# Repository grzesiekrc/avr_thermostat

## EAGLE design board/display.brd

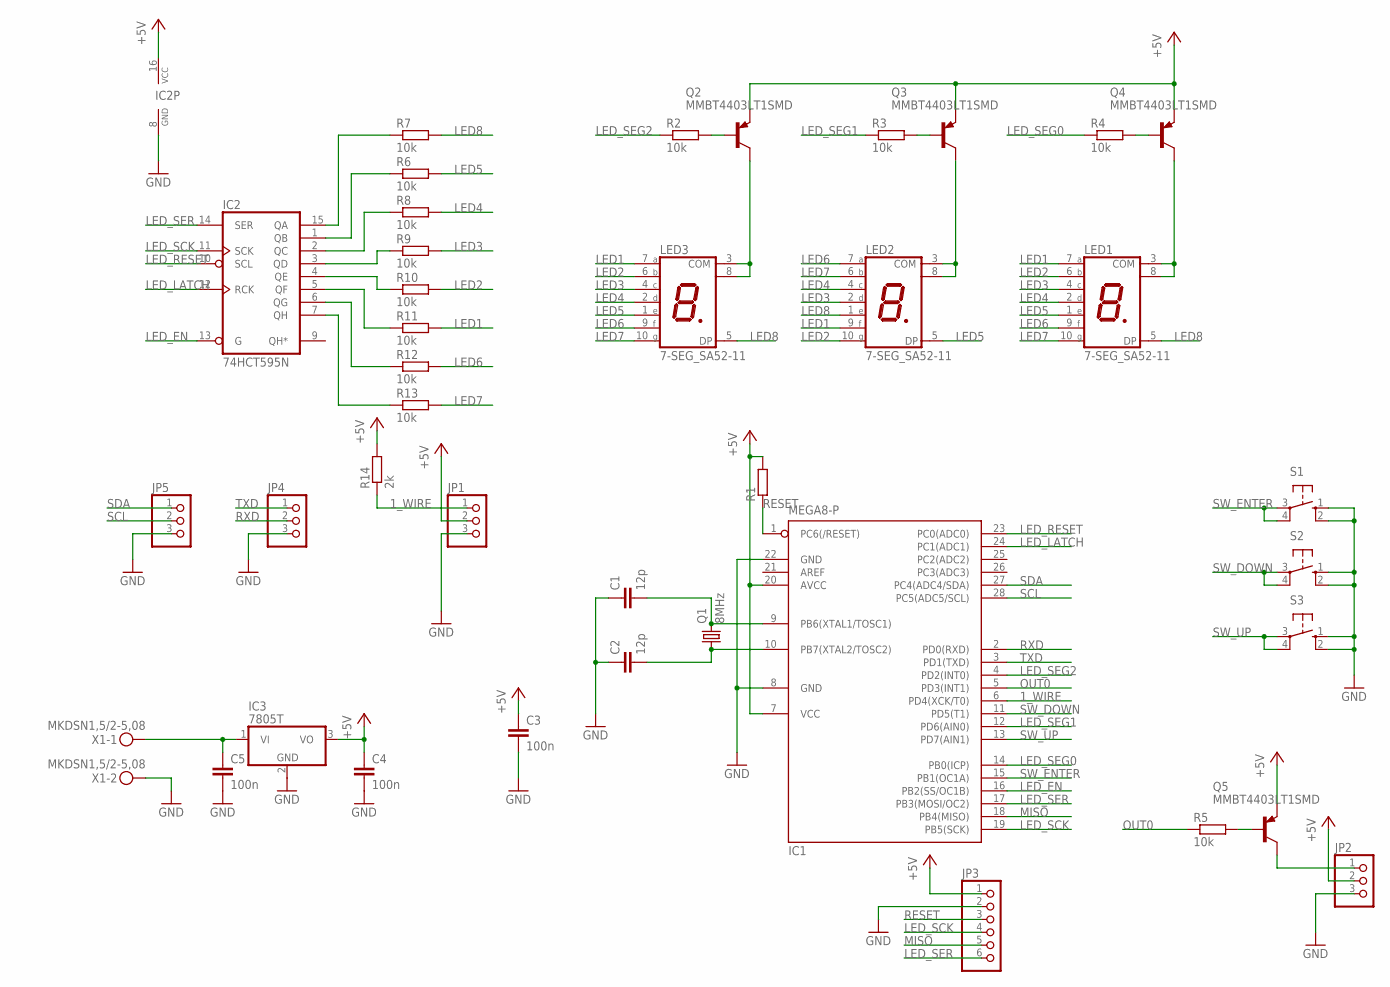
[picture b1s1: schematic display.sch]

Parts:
C1, C2: 12p; C050-035X075
C3, C4, C5: 100n; C050-030X075
IC1: MEGA8-P; DIL28-3
IC2: 74HCT595N; DIL16
IC3: 7805T; TO220H
JP1, JP2, JP4, JP5: PINHD-1X3; 1X03
JP3: PINHD-1X6; 1X06
LED1, LED2, LED3: 7-SEG_SA52-11; SA52-11
Q1: 8MHz; HC49U70
Q2, Q3, Q4, Q5: MMBT4403LT1SMD; SOT23-BEC
R1: R-EU_R1206; R1206
R2, R3, R4, R5, R6, R7, R8, R9, R10, R11, R12, R13: 10k; M1206
R14: 2k; M1206
S1, S2, S3: 10-XX; B3F-10XX
X1: MKDSN1,5/2-5,08

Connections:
1_WIRE: IC1.6 (PD4(XCK/T0)), JP1.1, R14.1
+5V: C3.1, C4.1, IC1.7 (VCC), IC1.20 (AVCC), IC2.16 (VCC), IC3.3 (VO), JP1.2, JP2.2, JP3.1, Q2.E, Q3.E, Q4.E, Q5.E, R1.2, R14.2
GND: C1.1, C2.1, C3.2, C4.2, C5.2, IC1.8 (GND), IC1.22 (GND), IC2.8 (GND), IC3.2 (GND), JP1.3, JP2.3, JP3.2, JP4.3, JP5.3, S1.1 (S), S1.2 (S1), S2.1 (S), S2.2 (S1), S3.1 (S), S3.2 (S1), X1.2
LED1: LED1.7 (A), LED2.9 (F), LED3.7 (A), R11.2
LED2: LED1.6 (B), LED2.10 (G), LED3.6 (B), R10.2
LED3: LED1.4 (C), LED2.2 (D), LED3.4 (C), R9.2
LED4: LED1.2 (D), LED2.4 (C), LED3.2 (D), R8.2
LED5: LED1.1 (E), LED2.5 (DP), LED3.1 (E), R6.2
LED6: LED1.9 (F), LED2.7 (A), LED3.9 (F), R12.2
LED7: LED1.10 (G), LED2.6 (B), LED3.10 (G), R13.2
LED8: LED1.5 (DP), LED2.1 (E), LED3.5 (DP), R7.2
LED_EN: IC1.16 (PB2(SS/OC1B)), IC2.13 (G)
LED_LATCH: IC1.24 (PC1(ADC1)), IC2.12 (RCK)
LED_RESET: IC1.23 (PC0(ADC0)), IC2.10 (SCL)
LED_SCK: IC1.19 (PB5(SCK)), IC2.11 (SCK), JP3.4
LED_SEG0: IC1.14 (PB0(ICP)), R4.1
LED_SEG1: IC1.12 (PD6(AIN0)), R3.1
LED_SEG2: IC1.4 (PD2(INT0)), R2.1
LED_SER: IC1.17 (PB3(MOSI/OC2)), IC2.14 (SER), JP3.6
MISO: IC1.18 (PB4(MISO)), JP3.5
unnamed: C1.2, IC1.9 (PB6(XTAL1/TOSC1)), Q1.2
unnamed: C2.2, IC1.10 (PB7(XTAL2/TOSC2)), Q1.1
unnamed: LED3.3 (COM), LED3.8 (COM), Q2.C
unnamed: IC2.15 (QA), R7.1
unnamed: LED1.3 (COM), LED1.8 (COM), Q4.C
unnamed: LED2.3 (COM), LED2.8 (COM), Q3.C
unnamed: Q2.B, R2.2
unnamed: Q3.B, R3.2
unnamed: Q4.B, R4.2
unnamed: Q5.B, R5.2
unnamed: JP2.1, Q5.C
unnamed: IC2.1 (QB), R6.1
unnamed: IC2.2 (QC), R8.1
unnamed: IC2.3 (QD), R9.1
unnamed: IC2.4 (QE), R10.1
unnamed: IC2.5 (QF), R11.1
unnamed: IC2.6 (QG), R12.1
unnamed: IC2.7 (QH), R13.1
unnamed: C5.1, IC3.1 (VI), X1.1
OUT0: IC1.5 (PD3(INT1)), R5.1
RESET: IC1.1 (PC6(/RESET)), JP3.3, R1.1
RXD: IC1.2 (PD0(RXD)), JP4.2
SCL: IC1.28 (PC5(ADC5/SCL)), JP5.2
SDA: IC1.27 (PC4(ADC4/SDA)), JP5.1
SW_DOWN: IC1.11 (PD5(T1)), S2.3, S2.4 (P1)
SW_ENTER: IC1.15 (PB1(OC1A)), S1.3, S1.4 (P1)
SW_UP: IC1.13 (PD7(AIN1)), S3.3, S3.4 (P1)
TXD: IC1.3 (PD1(TXD)), JP4.1

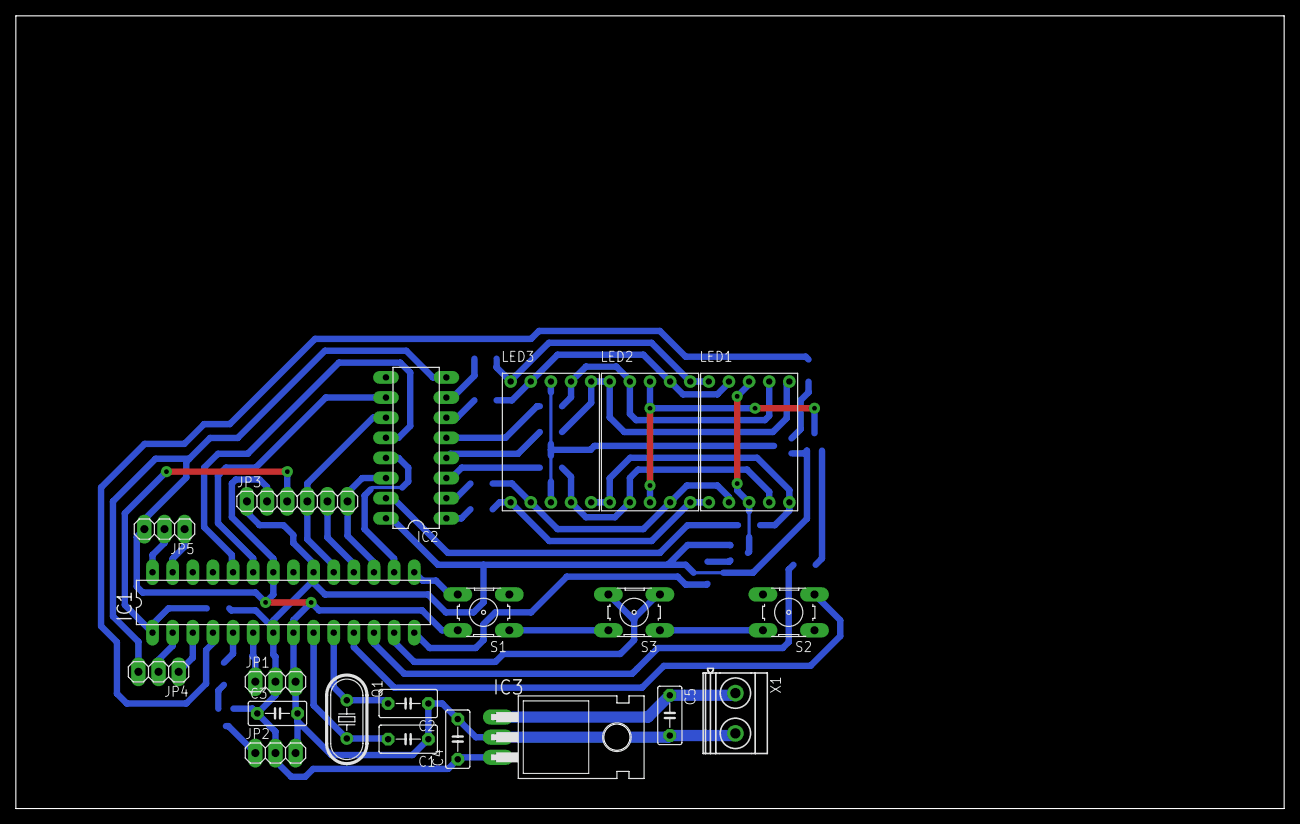
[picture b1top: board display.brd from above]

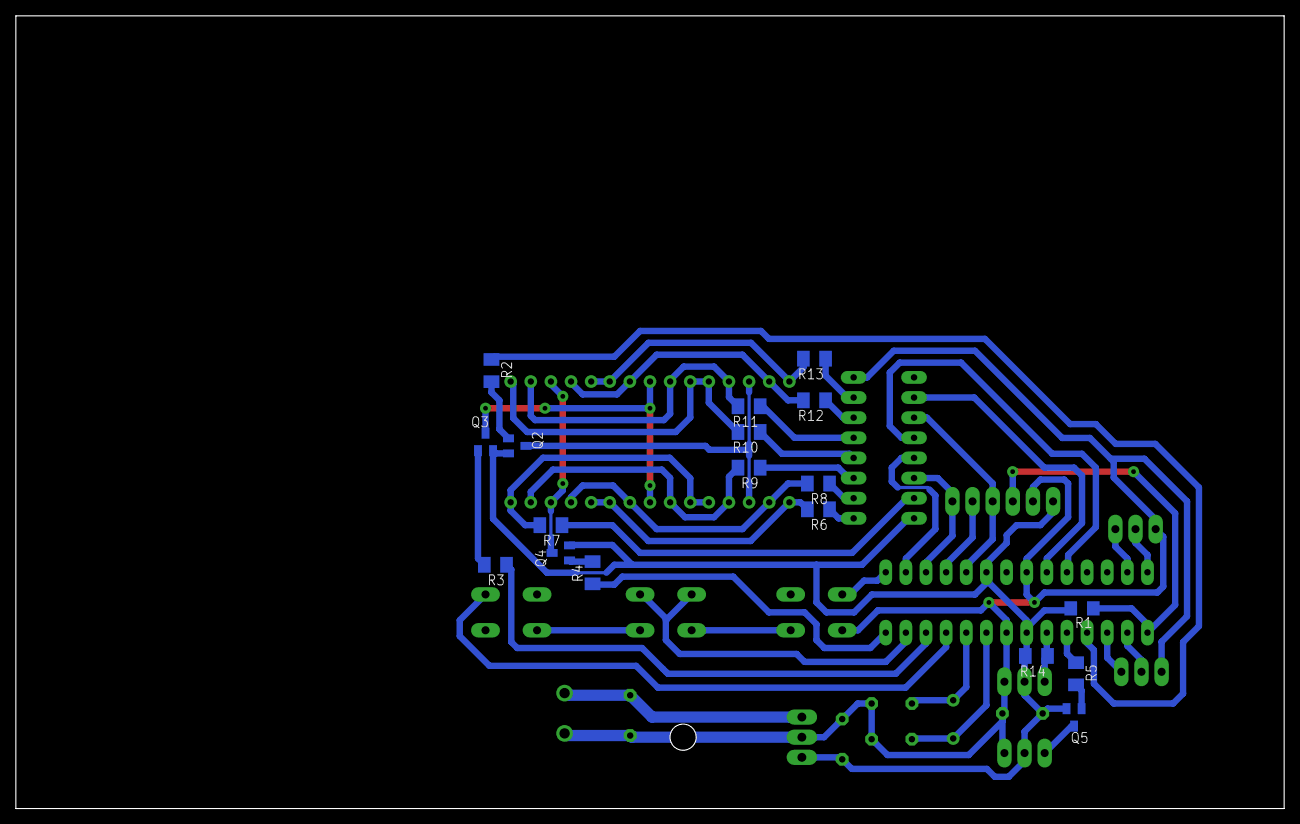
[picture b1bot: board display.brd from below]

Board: 2 copper layers, 160.0 x 100.0 mm, 39 parts (18 on the bottom side), 48 nets.

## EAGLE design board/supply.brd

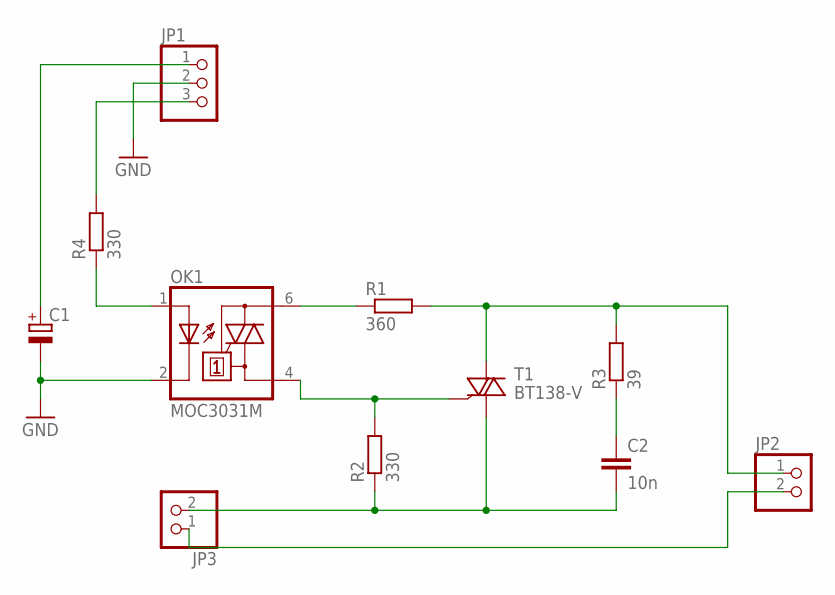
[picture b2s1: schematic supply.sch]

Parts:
C1: CPOL-EUE5-10.5; E5-10,5
C2: 10n; C102-064X133
JP1: PINHD-1X3; 1X03
JP2, JP3: PINHD-1X2; 1X02
OK1: MOC3031M; DIL06
R1: 360; 0207/10
R2, R4: 330; 0207/10
R3: 39; 0207/10
T1: BT138-V; TO220BV

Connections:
GND: C1.-, JP1.2, OK1.2 (C)
unnamed: OK1.1 (A), R4.1
unnamed: OK1.6 (A2), R1.1
unnamed: JP2.1, R1.2, R3.2, T1.T2 (A2)
unnamed: OK1.4 (A1), R2.2, T1.G
unnamed: C2.2, JP3.2, R2.1, T1.T1 (A1)
unnamed: C2.1, R3.1
unnamed: JP1.3, R4.2
unnamed: C1.+, JP1.1
unnamed: JP2.2, JP3.1

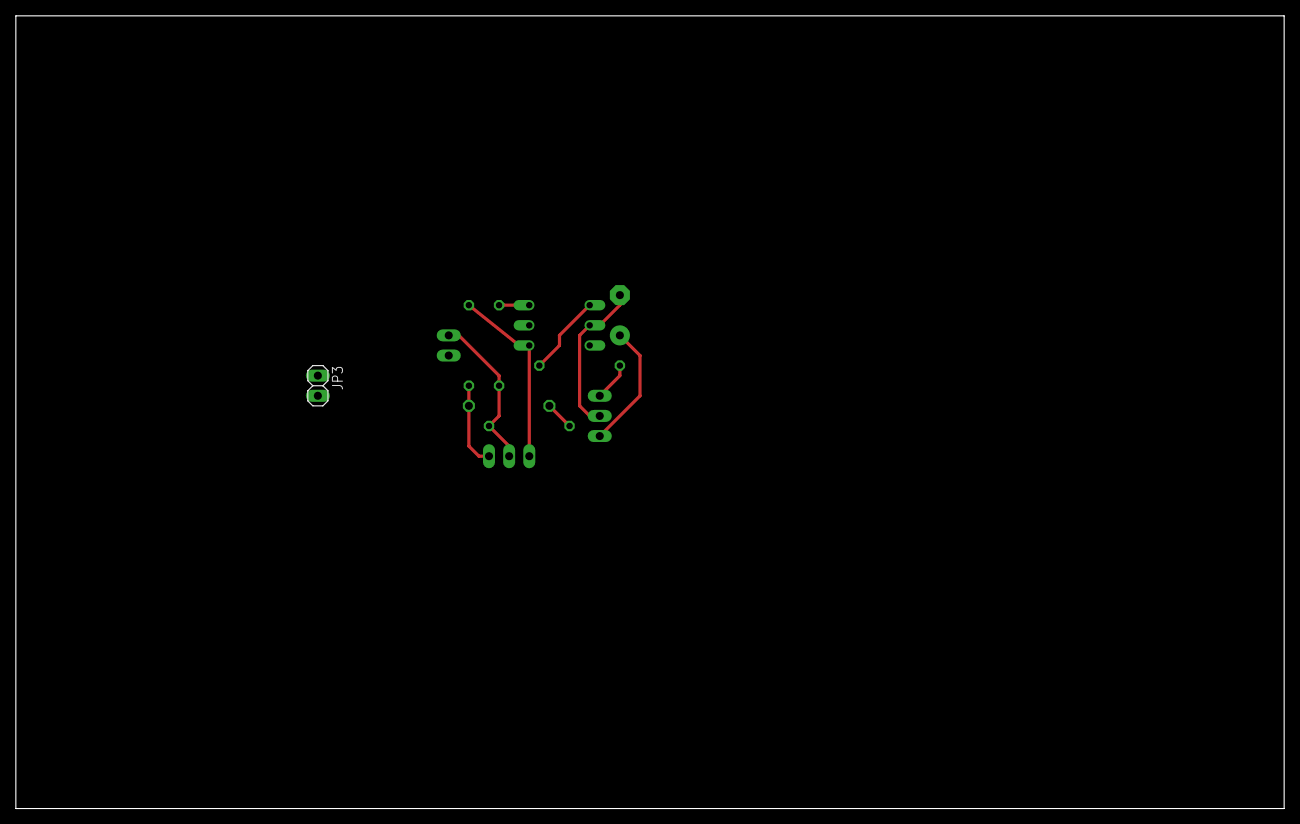
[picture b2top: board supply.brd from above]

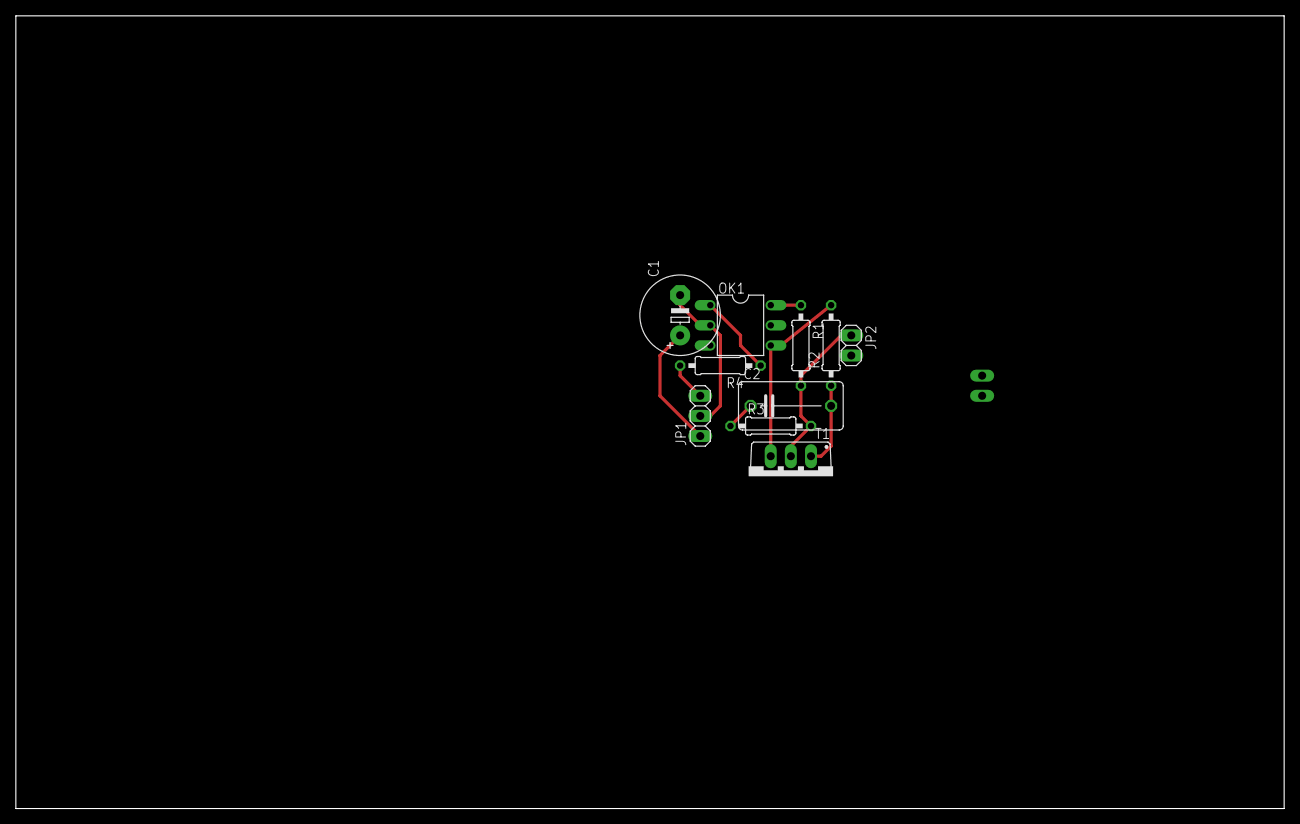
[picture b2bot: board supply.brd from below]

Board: 2 copper layers, 160.0 x 100.0 mm, 11 parts (10 on the bottom side), 10 nets.

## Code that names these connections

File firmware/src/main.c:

/*
 * main.c
 *
 *  Created on: 14 wrz 2023
 *      Author: grzesiek
 */

#include <avr/io.h>
#include <avr/interrupt.h>

#include "1wire.h"
#include "display.h"
#include "output_control.h"
#include "buttons.h"
#include "utils.h"
int16_t temperature = 0;

volatile uint8_t timCounter;
volatile uint8_t seconds = 0;

ISR(TIMER0_OVF_vect)
{
	if(++timCounter > TIM_SECOND_COUNTER_MAX)
	{
		seconds++;
		timCounter = 0;
	}
}

void sendByte(uint8_t byte)
{
	while (!(UCSRA & (1<<UDRE)));
	UDR = byte;
}

void printTemperature(int16_t value)
{
	if (value < 0)
	{
		sendByte('-');
		value *= -1;
	}

	uint8_t digits[10];
	int8_t i = 0;

	while (value > 0)
	{
		digits[i++] = (value % 10) + '0';
		value /= 10;
	}

	i--;

	while (i > 0)
	{
		sendByte(digits[i--]);
	}
	sendByte('.');
	sendByte(digits[0]);
	sendByte('*');//Celsius degree sign
	sendByte('C');
}

void processTimer(void)
{
	static uint16_t prevSeconds;
	if(prevSeconds != seconds)
	{
		displaySecondElapsed();
		prevSeconds = seconds;
		sendByte('\r');
		printTemperature(temperature);
		sendByte(' ');
		sendByte(' ');
		sendByte(' ');
	}
}

int main(void)
{
	DDRB = (1<<PB0) | (1<<PB2) | (1<<PB3) | (1<<PB5);
	DDRC = (1<<PC0) | (1<<PC1);
	DDRD = (1<<PD1) | (1<<PD2) | (1<<PD3) | (1<<PD6);
	PORTD = (1<<PD5) | (1<<PD7);

	PORTB = (1<<PB1);

	UBRRH = 0;
	UBRRL = (unsigned char)51;

	//UCSRB = (1<<TXEN) | (1<<RXEN) | (1<<TXCIE) | (1<<RXCIE) | (1<<UCSZ2);
	UCSRB = (1<<TXEN) | (1<<RXEN) | (1<<RXCIE);
	UCSRC = (1<<URSEL) | (1<<UCSZ1) | (1<<UCSZ0);

	TCCR0 = (1<<CS02) | (1<<CS00);

	TCCR1A = (1<<WGM10) | (1<<COM1B1) | (1<<COM1B0);
	TCCR1B = (1<<WGM12) | (1<<CS11) | (1<<CS10);

	TIMSK = (1<<TOIE0);

	SPCR = (1<<SPIE) | (1<<SPE) | (1<<MSTR) | (1<<SPR1) | (1<<SPR0);

	BRIGHTNESS(255);

	OUTPUT_OFF();

	sei();

	displayInit();

	while(1)
	{
		temperature = readTemperature();
		temperatureNotification(temperature);
		processButtons();
		processTimer();
		processDisplay();
	}
}

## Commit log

2023-10-08 complete board and display current temperature
2023-10-08 working buttons and set temperature
2023-10-13 configure mode
2023-10-17 handle default 85*C value
